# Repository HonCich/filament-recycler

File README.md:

# filament-recyclator
 
## About project
 The goal of the work is design and implementation of a machine for production and recyclation of 3D printing material for FDM 3D printers (filament). The emphasis is put on the simplicity of the resulting device and the ease of its production process.

 I started working on this project at the end of summer 2021 with great help from Ing. Martin Ptáček. It started as my project for Středoškolská odborná činnost, which is science competetion held in the Czech Republic. After this competetion I decided to continue and further upgrade this machine.

 At this moment project contains working designs of filament extruder, filament puller, electronics board and software.

## 3D models
[Extruder 3D model](https://cad.onshape.com/documents/50d4ffc71355bbf60bf18542/w/1bb6894ef7bc64ec395a8974/e/ffa39023716e79eba0ffd74a)

[Gearbox 3D model](https://cad.onshape.com/documents/cd74832d7d2c633c7039baa6/w/958712d359a12f9b1e2d2bfe/e/a4a0fd0a7c25512e608e8250)

[Filament puller 3D model](https://cad.onshape.com/documents/47426692b6b663d8016df0e7/w/ed22a120c506776f4e319dcb/e/ad41a19a2c0e068ddb01ab12)

## Licence
* Contents of this repository except *software* folder are shared under [Attribution-NonCommercial-ShareAlike 4.0 International (CC BY-NC-SA 4.0)](https://creativecommons.org/licenses/by-nc-sa/4.0/) licence.
* Contents of *software* folder are shared under [GNU Lesser General Public License v3.0](https://www.gnu.org/licenses/lgpl-3.0.en.html) licence.

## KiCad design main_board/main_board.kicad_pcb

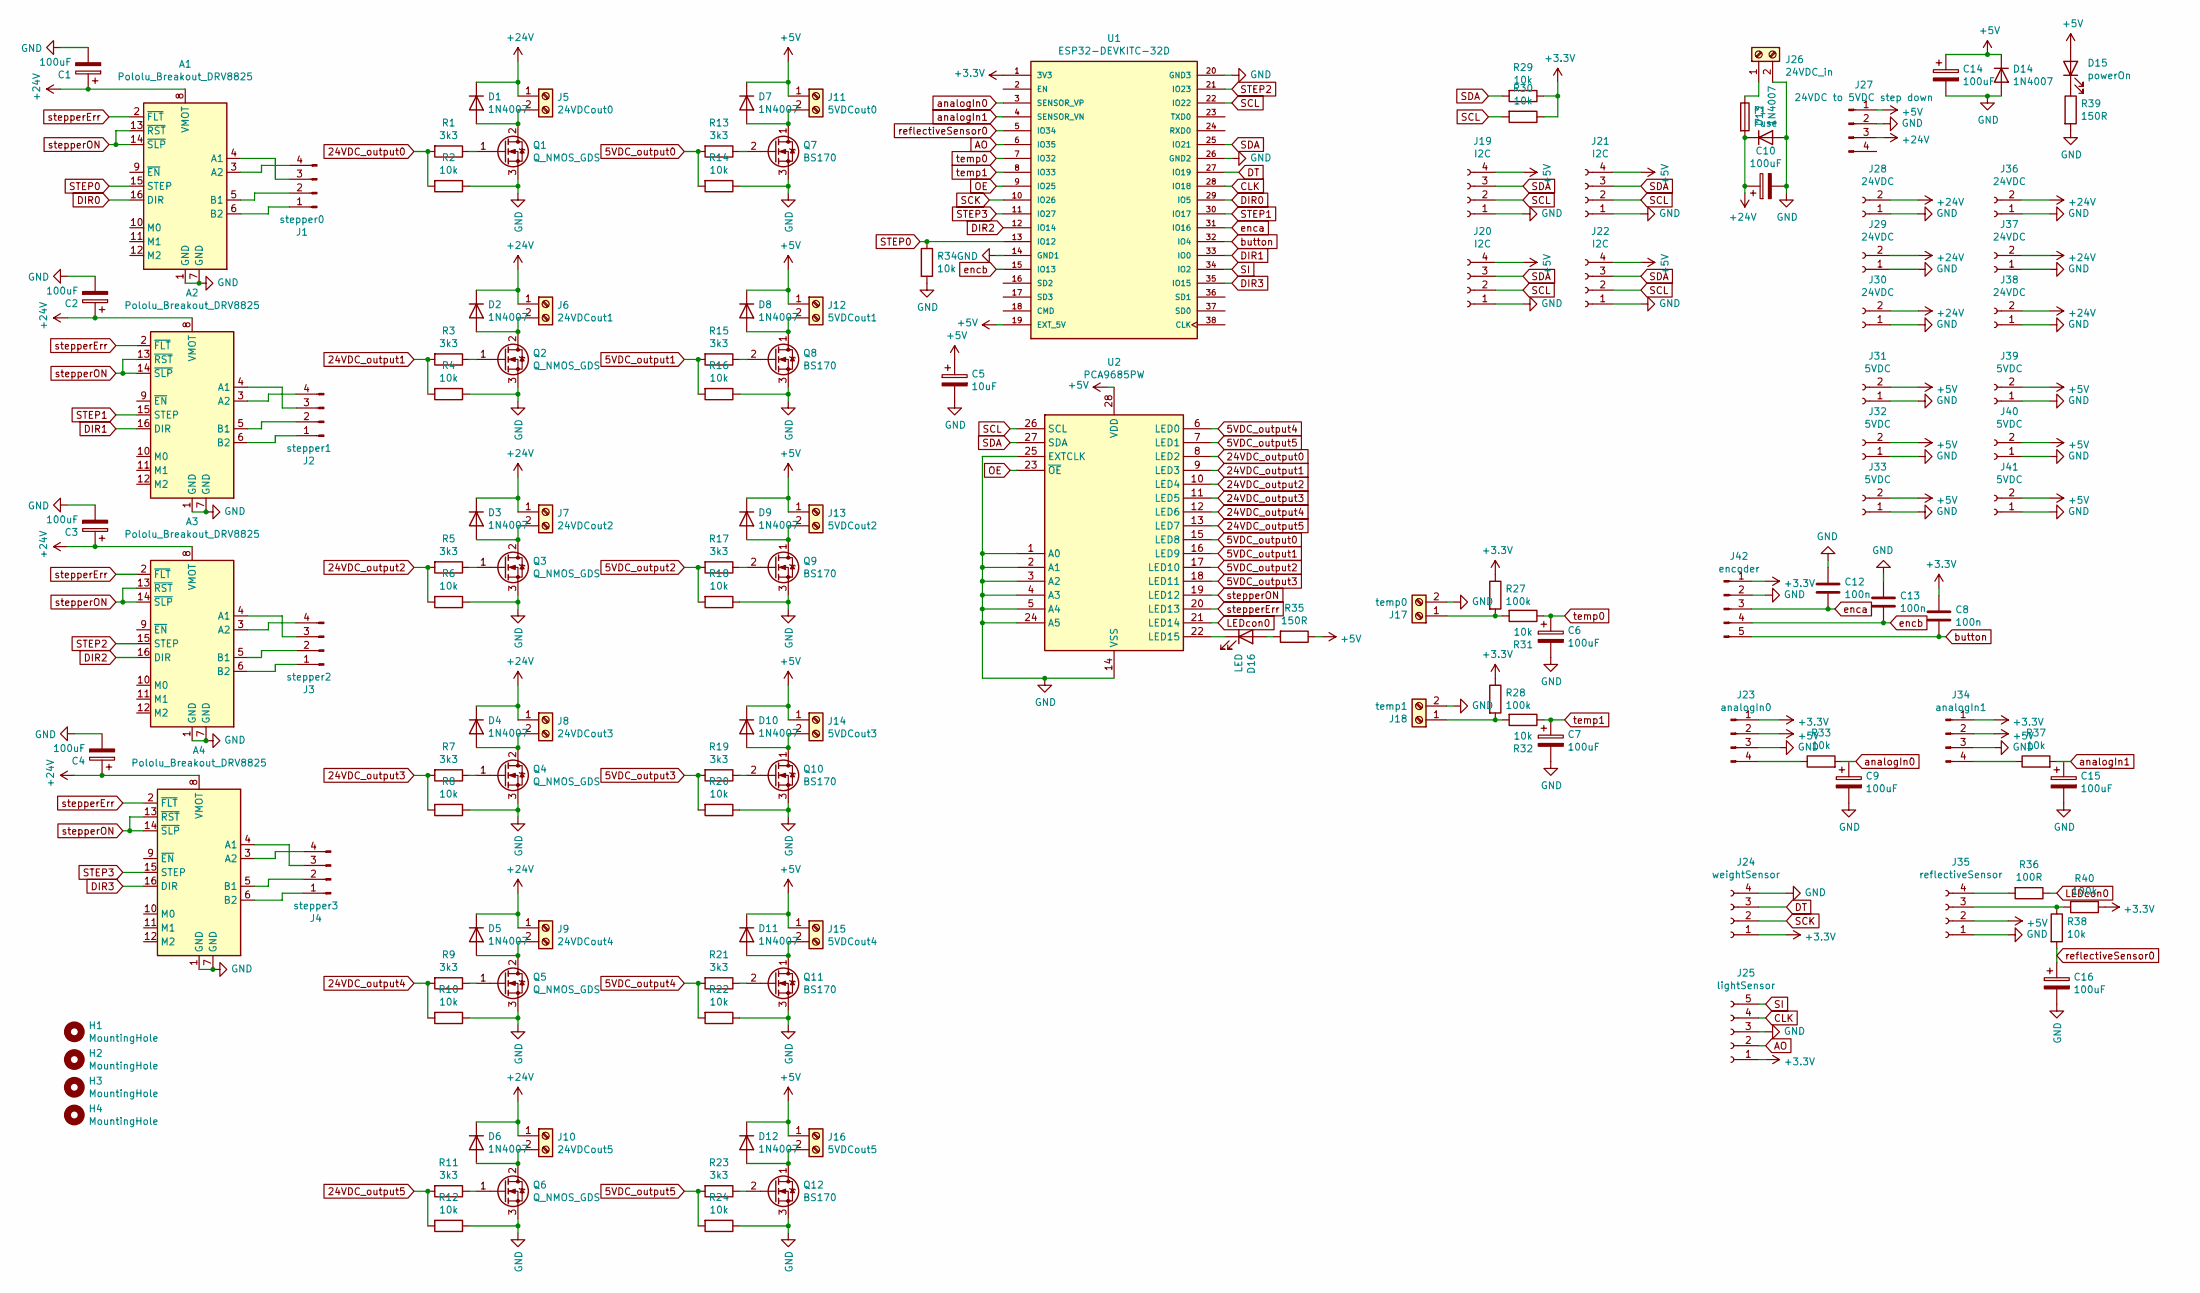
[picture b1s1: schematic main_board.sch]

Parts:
A1, A2, A3, A4: Pololu_Breakout_DRV8825; Pololu_Breakout-16_15.2x20.3mm
C1, C2, C3, C4, C6, C7, C9, C10, C14, C15, C16: 100uF; CP_Radial_D6.3mm_P2.50mm
C5: 10uF; CP_Radial_D6.3mm_P2.50mm
C8, C12, C13: 100n; C_1206_3216Metric_Pad1.33x1.80mm_HandSolder
D1, D2, D3, D4, D5, D6, D7, D8, D9, D10, D11, D12, D13, D14: 1N4007; D_DO-15_P2.54mm_Vertical_AnodeUp
D15: powerOn; LED_D3.0mm
D16: LED; LED_D3.0mm
F1: Fuse; Fuseholder_Cylinder-5x20mm_Schurter_0031_8201_Horizontal_Op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
H1, H2, H3, H4: MountingHole; MountingHole_3.2mm_M3
J1: stepper0; PinHeader_1x04_P2.54mm_Vertical
J2: stepper1; PinHeader_1x04_P2.54mm_Vertical
J3: stepper2; PinHeader_1x04_P2.54mm_Vertical
J4: stepper3; PinHeader_1x04_P2.54mm_Vertical
J5: 24VDCout0; TerminalBlock_bornier-2_P5.08mm
J6: 24VDCout1; TerminalBlock_bornier-2_P5.08mm
J7: 24VDCout2; TerminalBlock_bornier-2_P5.08mm
J8: 24VDCout3; TerminalBlock_bornier-2_P5.08mm
J9: 24VDCout4; TerminalBlock_bornier-2_P5.08mm
J10: 24VDCout5; TerminalBlock_bornier-2_P5.08mm
J11: 5VDCout0; TerminalBlock_bornier-2_P5.08mm
J12: 5VDCout1; TerminalBlock_bornier-2_P5.08mm
J13: 5VDCout2; TerminalBlock_bornier-2_P5.08mm
J14: 5VDCout3; TerminalBlock_bornier-2_P5.08mm
J15: 5VDCout4; TerminalBlock_bornier-2_P5.08mm
J16: 5VDCout5; TerminalBlock_bornier-2_P5.08mm
J17: temp0; TerminalBlock_bornier-2_P5.08mm
J18: temp1; TerminalBlock_bornier-2_P5.08mm
J19, J20, J21, J22: I2C; PinHeader_1x04_P2.54mm_Vertical
J23: analogIn0; PinHeader_1x04_P2.54mm_Vertical
J24: weightSensor; PinHeader_1x04_P2.54mm_Vertical
J25: lightSensor; PinHeader_1x05_P2.54mm_Vertical
J26: 24VDC_in; TerminalBlock_bornier-2_P5.08mm
J27: 24VDC to 5VDC step down; PinHeader_1x04_P2.54mm_Vertical
J28, J29, J30, J36, J37, J38: 24VDC; PinHeader_1x02_P2.54mm_Vertical
J31, J32, J33, J39, J40, J41: 5VDC; PinHeader_1x02_P2.54mm_Vertical
J34: analogIn1; PinHeader_1x04_P2.54mm_Vertical
J35: reflectiveSensor; PinHeader_1x04_P2.54mm_Vertical
J42: encoder; PinHeader_1x05_P2.54mm_Vertical
Q1, Q2, Q3, Q4, Q5, Q6: Q_NMOS_GDS; TO-220-3_Vertical
Q7, Q8, Q9, Q10, Q11, Q12: BS170; TO-92_Inline_Wide
R1, R3, R5, R7, R9, R11, R13, R15, R17, R19, R21, R23: 3k3; R_1206_3216Metric_Pad1.30x1.75mm_HandSolder
R2, R4, R6, R8, R10, R12, R14, R16, R18, R20, R22, R24, R29, R30, R31, R32, R33, R34, R37, R38: 10k; R_1206_3216Metric_Pad1.30x1.75mm_HandSolder
R27, R28, R40: 100k; R_1206_3216Metric_Pad1.30x1.75mm_HandSolder
R35, R39: 150R; R_1206_3216Metric_Pad1.30x1.75mm_HandSolder
R36: 100R; R_1206_3216Metric_Pad1.30x1.75mm_HandSolder
U1: ESP32-DEVKITC-32D; MODULE_ESP32-DEVKITC-32D; PARTREV 4
U2: PCA9685PW; TSSOP-28_4.4x9.7mm_P0.65mm

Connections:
5VDC_output0: R13.2, R14.2, U2.15 (LED8)
5VDC_output1: R15.2, R16.2, U2.16 (LED9)
5VDC_output2: R17.2, R18.2, U2.17 (LED10)
5VDC_output3: R19.2, R20.2, U2.18 (LED11)
5VDC_output4: R21.2, R22.2, U2.6 (LED0)
5VDC_output5: R23.2, R24.2, U2.7 (LED1)
24VDC_output0: R1.2, R2.2, U2.8 (LED2)
24VDC_output1: R3.2, R4.2, U2.9 (LED3)
24VDC_output2: R5.2, R6.2, U2.10 (LED4)
24VDC_output3: R7.2, R8.2, U2.11 (LED5)
24VDC_output4: R9.2, R10.2, U2.12 (LED6)
24VDC_output5: R11.2, R12.2, U2.13 (LED7)
+3V3: C8.2, J23.1, J24.1, J25.1, J34.1, J42.1, R27.1, R28.1, R29.1, R30.1, R40.1, U1.1 (3V3)
+5V: C5.1, C14.1, D7.1 (K), D8.1 (K), D9.1 (K), D10.1 (K), D11.1 (K), D12.1 (K), D14.1 (K), D15.2 (A), J11.1, J12.1, J13.1, J14.1, J15.1, J16.1, J19.4, J20.4, J21.4, J22.4, J23.2, J27.1, J31.2, J32.2, J33.2, J34.2, J35.2, J39.2, J40.2, J41.2, R35.1, U1.19 (EXT_5V), U2.28 (VDD)
+24V: A1.8 (VMOT), A2.8 (VMOT), A3.8 (VMOT), A4.8 (VMOT), C1.1, C2.1, C3.1, C4.1, C10.1, D1.1 (K), D2.1 (K), D3.1 (K), D4.1 (K), D5.1 (K), D6.1 (K), D13.1 (K), F1.2, J5.1, J6.1, J7.1, J8.1, J9.1, J10.1, J27.3, J28.2, J29.2, J30.2, J36.2, J37.2, J38.2
AO: J25.2, U1.6 (IO35)
CLK: J25.4, U1.28 (IO18)
DIR0: A1.16 (DIR), U1.29 (IO5)
DIR1: A2.16 (DIR), U1.33 (IO0)
DIR2: A3.16 (DIR), U1.12 (IO14)
DIR3: A4.16 (DIR), U1.35 (IO15)
DT: J24.3, U1.27 (IO19)
GND: A1.1 (GND), A1.7 (GND), A2.1 (GND), A2.7 (GND), A3.1 (GND), A3.7 (GND), A4.1 (GND), A4.7 (GND), C1.2, C2.2, C3.2, C4.2, C5.2, C6.2, C7.2, C9.2, C10.2, C12.2, C13.2, C14.2, C15.2, C16.2, D13.2 (A), D14.2 (A), J17.2, J18.2, J19.1, J20.1, J21.1, J22.1, J23.3, J24.4, J25.3, J26.2, J27.2, J28.1, J29.1, J30.1, J31.1, J32.1, J33.1, J34.3, J35.1, J36.1, J37.1, J38.1, J39.1, J40.1, J41.1, J42.2, Q1.3 (S), Q2.3 (S), Q3.3 (S), Q4.3 (S), Q5.3 (S), Q6.3 (S), Q7.3 (S), Q8.3 (S), Q9.3 (S), Q10.3 (S), Q11.3 (S), Q12.3 (S), R2.1, R4.1, R6.1, R8.1, R10.1, R12.1, R14.1, R16.1, R18.1, R20.1, R22.1, R24.1, R34.2, R39.2, U1.14 (GND1), U1.20 (GND3), U1.26 (GND2), U2.1 (A0), U2.2 (A1), U2.3 (A2), U2.4 (A3), U2.5 (A4), U2.14 (VSS), U2.24 (A5), U2.25 (EXTCLK)
LEDcon0: R36.1, U2.21 (LED14)
unnamed: A1.3 (A2), J1.4
unnamed: A1.4 (A1), J1.3
unnamed: A1.5 (B1), J1.2
unnamed: A1.6 (B2), J1.1
unnamed: A2.3 (A2), J2.4
unnamed: A2.4 (A1), J2.3
unnamed: A2.5 (B1), J2.2
unnamed: A2.6 (B2), J2.1
unnamed: A3.3 (A2), J3.4
unnamed: A3.4 (A1), J3.3
unnamed: A3.5 (B1), J3.2
unnamed: A3.6 (B2), J3.1
unnamed: A4.3 (A2), J4.4
unnamed: A4.4 (A1), J4.3
unnamed: A4.5 (B1), J4.2
unnamed: A4.6 (B2), J4.1
unnamed: D1.2 (A), J5.2, Q1.2 (D)
unnamed: D2.2 (A), J6.2, Q2.2 (D)
unnamed: D3.2 (A), J7.2, Q3.2 (D)
unnamed: D4.2 (A), J8.2, Q4.2 (D)
unnamed: D5.2 (A), J9.2, Q5.2 (D)
unnamed: D6.2 (A), J10.2, Q6.2 (D)
unnamed: D7.2 (A), J11.2, Q7.1 (D)
unnamed: D8.2 (A), J12.2, Q8.1 (D)
unnamed: D9.2 (A), J13.2, Q9.1 (D)
unnamed: D10.2 (A), J14.2, Q10.1 (D)
unnamed: D11.2 (A), J15.2, Q11.1 (D)
unnamed: D12.2 (A), J16.2, Q12.1 (D)
unnamed: D15.1 (K), R39.1
unnamed: D16.1 (K), U2.22 (LED15)
unnamed: D16.2 (A), R35.2
unnamed: F1.1, J26.1
unnamed: J17.1, R27.2, R31.2
unnamed: J18.1, R28.2, R32.2
unnamed: J23.4, R33.1
unnamed: J34.4, R37.1
unnamed: J35.3, R38.1, R40.2
unnamed: J35.4, R36.2
unnamed: Q1.1 (G), R1.1
unnamed: Q2.1 (G), R3.1
unnamed: Q3.1 (G), R5.1
unnamed: Q4.1 (G), R7.1
unnamed: Q5.1 (G), R9.1
unnamed: Q6.1 (G), R11.1
unnamed: Q7.2 (G), R13.1
unnamed: Q8.2 (G), R15.1
unnamed: Q9.2 (G), R17.1
unnamed: Q10.2 (G), R19.1
unnamed: Q11.2 (G), R21.1
unnamed: Q12.2 (G), R23.1
OE: U1.9 (IO25), U2.23 (~OE)
SCK: J24.2, U1.10 (IO26)
SCL: J19.2, J20.2, J21.2, J22.2, R30.2, U1.22 (IO22), U2.26 (SCL)
SDA: J19.3, J20.3, J21.3, J22.3, R29.2, U1.25 (IO21), U2.27 (SDA)
SI: J25.5, U1.34 (IO2)
STEP0: A1.15 (STEP), R34.1, U1.13 (IO12)
STEP1: A2.15 (STEP), U1.30 (IO17)
STEP2: A3.15 (STEP), U1.21 (IO23)
STEP3: A4.15 (STEP), U1.11 (IO27)
analogIn0: R33.2, U1.3 (SENSOR_VP)
analogIn1: R37.2, U1.4 (SENSOR_VN)
button: C8.1, J42.5, U1.32 (IO4)
enca: C12.1, J42.3, U1.31 (IO16)
encb: C13.1, J42.4, U1.15 (IO13)
reflectiveSensor0: C16.1, R38.2, U1.5 (IO34)
stepperErr: A1.2 (~FLT), A2.2 (~FLT), A3.2 (~FLT), A4.2 (~FLT), U2.20 (LED13)
stepperON: A1.13 (~RST), A1.14 (~SLP), A2.13 (~RST), A2.14 (~SLP), A3.13 (~RST), A3.14 (~SLP), A4.13 (~RST), A4.14 (~SLP), U2.19 (LED12)
temp0: C6.1, R31.1, U1.7 (IO32)
temp1: C7.1, R32.1, U1.8 (IO33)

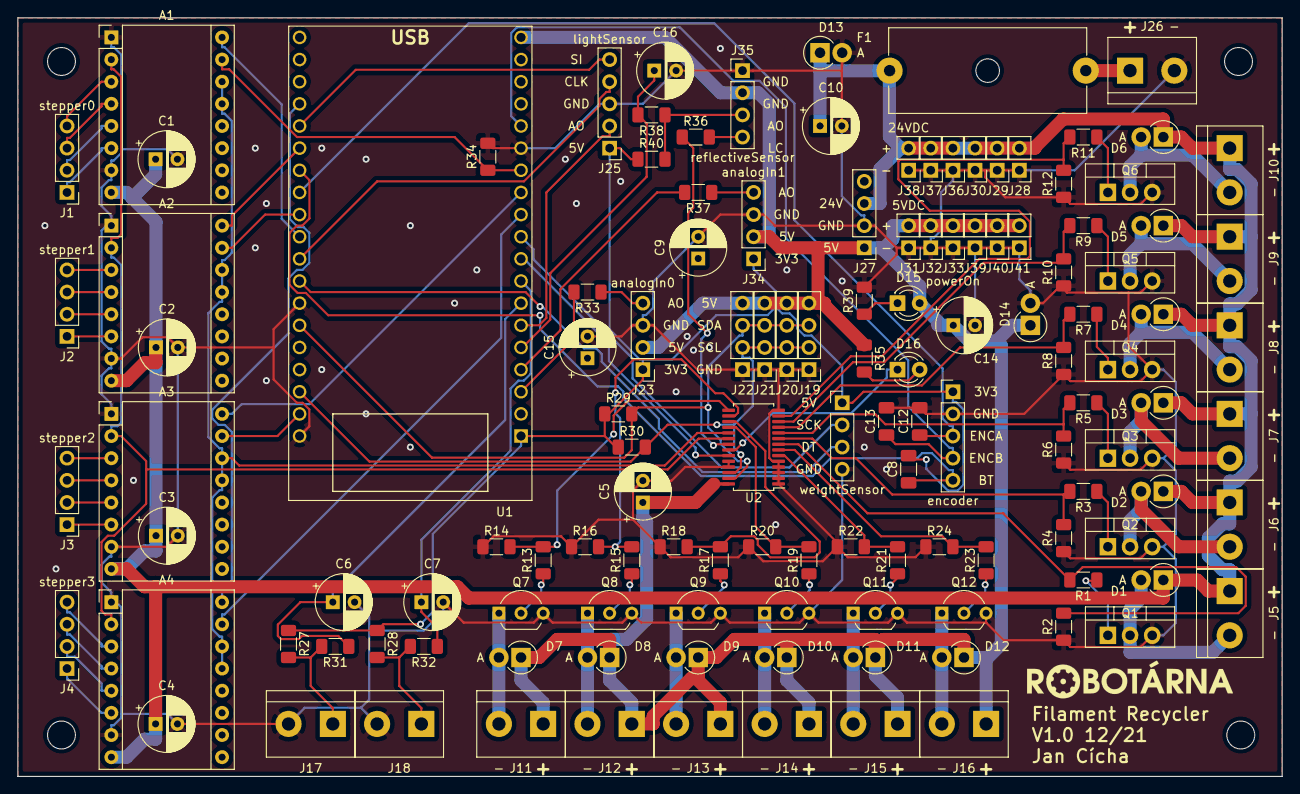
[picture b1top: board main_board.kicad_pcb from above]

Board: 2 copper layers, 145.0 x 87.0 mm, 134 parts (0 on the bottom side), 93 nets.

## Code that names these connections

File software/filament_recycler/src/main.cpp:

#include <Arduino.h>
#include <HardwareSerial.h>
#include "Wire.h"
#include "PCA9685.h"
#include "HX711.h"
#include "AccelStepper.h"
#include "MultiStepper.h"


const uint8_t reflectivesensor0 = 34;
const uint8_t PCA_OE = 25;
const uint8_t stepperON = 12;
const uint8_t LEDsign = 15;
const uint8_t step0 = 12;
const uint8_t dir0 = 5;
const uint8_t step1 = 17;
const uint8_t dir1 = 0;
char tempPin[2]={32,33};
char fiveVPin[6]={8,9,10,11,0,1};
char twentyFourVPin[6]={2,3,4,5,6,7};

int prevTime = 0;

const float c1 = 0.0007157730988481782;
const float c2 = 0.0002145860245372531;
const float c3 = 1.0991444718982721e-7;

PCA9685 PCA(0x70);
AccelStepper stepper0(AccelStepper::DRIVER, step0, dir0);
AccelStepper stepper1(AccelStepper::DRIVER, step1, dir1);

void outputEnable (bool enable);
void fiveVDrive (uint8_t output, int value);
void twentyFourVDrive (uint8_t output, int value);
int reflectiveRead ();
float tempRead (uint8_t temp);

void outputEnable (bool enable)
{
    digitalWrite(PCA_OE, !enable);
    PCA.digitalWrite(stepperON,enable);
    PCA.digitalWrite(LEDsign,enable);
}

void fiveVDrive (uint8_t output, int value)
{
  PCA.setPWM(fiveVPin[output],0+value*40.95);
}

void twentyFourVDrive (uint8_t output, int value)
{
  PCA.setPWM(twentyFourVPin[output],0+value*40.95);
}

int reflectiveRead ()
{
  PCA.setON(14);
  return analogRead(reflectivesensor0);
}

float tempRead (uint8_t temp)
{
  float R,T,logR;
  R = 100000 / (4095.0 / analogRead(tempPin[temp]) - 1.0);
  logR = log(R);
  T = (1 / (c1 + c2 * logR + c3 * logR * logR * logR)) - 273.15;
  Serial.println(T);
  return(T);
}

void setup() {
  // put your setup code here, to run once:
  Serial.begin(9600);
  Wire.begin(); 
  PCA.begin();

  outputEnable(1);
  stepper0.setAcceleration(200.0);
  stepper0.setMaxSpeed(1000);
  stepper0.setSpeed(200);
  stepper1.setAcceleration(200.0);
  stepper1.setMaxSpeed(1000);
  stepper1.setSpeed(2);

  twentyFourVDrive(0,80);
  twentyFourVDrive(1,80);
  /*while (tempRead(0)<260)
  {
    delay(1000);
  }
  
  prevTime = millis();*/
}


void loop() {
  // put your main code here, to run repeatedly
  /*if (millis()-prevTime>=1000)
  {
    if(tempRead(0)<300)
    {
      twentyFourVDrive(0,100);
      twentyFourVDrive(1,100);
    }
    else
    {
      twentyFourVDrive(0,0);
      twentyFourVDrive(1,0);
    }
    prevTime=millis();
  }*/
  
stepper0.runSpeed();
stepper1.runSpeed();
}

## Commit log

2021-02-03 started main board schematic
2021-04-22 started board
2021-11-24 added parts to scheme
2021-11-29 schematic update
2021-11-30 footprints assigned
2021-12-05 PCB started
2021-12-06 PCB v1
2021-12-07 PCB changes
2021-12-08 routs added
2021-12-08 making pcb smaller
2021-12-09 PCB update
2021-12-09 added routs
2021-12-12 added gnd zones
2021-12-13 part names moved
2021-12-13 part numbers added
2021-12-14 GND zones added
2021-12-14 GND zone update
2021-12-14 production files generated
2021-12-14 ADC 2 unused
2021-12-15 problems fix
2021-12-15 bug fix
2021-12-15 reroute
2021-12-15 reflectiveSensor
2022-01-13 software
2022-01-28 motor problem
2022-02-13 problem s topenim
2022-04-08 licence přidána
2022-09-30 Added project description
